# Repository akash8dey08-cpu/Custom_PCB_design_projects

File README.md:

# Embedded Hardware & PCB Design Portfolio (KiCad)

A collection of custom 2-layer printed circuit boards designed in KiCad for power regulation, STM32 sensor telemetry, and analog signal conditioning.

## Projects Index

| Project | Key ICs / Components | Layers | Directory |
| :--- | :--- | :--- | :--- |
| **1. Dual-Input Buck + LDO Power Supply** | `LM2596T-ADJ`, `MIC29152WT`, `1N5822`, USB-C + Barrel Jack | 2-Layer | [`/01-Dual-Input-Power-Supply`](Dual-Input-Power-Supply) |
| **2. STM32 Blackpill Sensor Carrier** | `AMS1117-3.3`, `MPU6050`, `BME280`, `HC-SR04`, `DHT22` | 2-Layer | [`/02-Blackpill-Sensor-Carrier`](LDR_Sensor_Breakout) |
| **3. LDR07 Light Sensor Breakout** | `LDR07`, `10k` Divider, 3-Pin Header | 2-Layer | [`/03-LDR07-Light-Sensor-Breakout`](STM_sensor_hub) |

---

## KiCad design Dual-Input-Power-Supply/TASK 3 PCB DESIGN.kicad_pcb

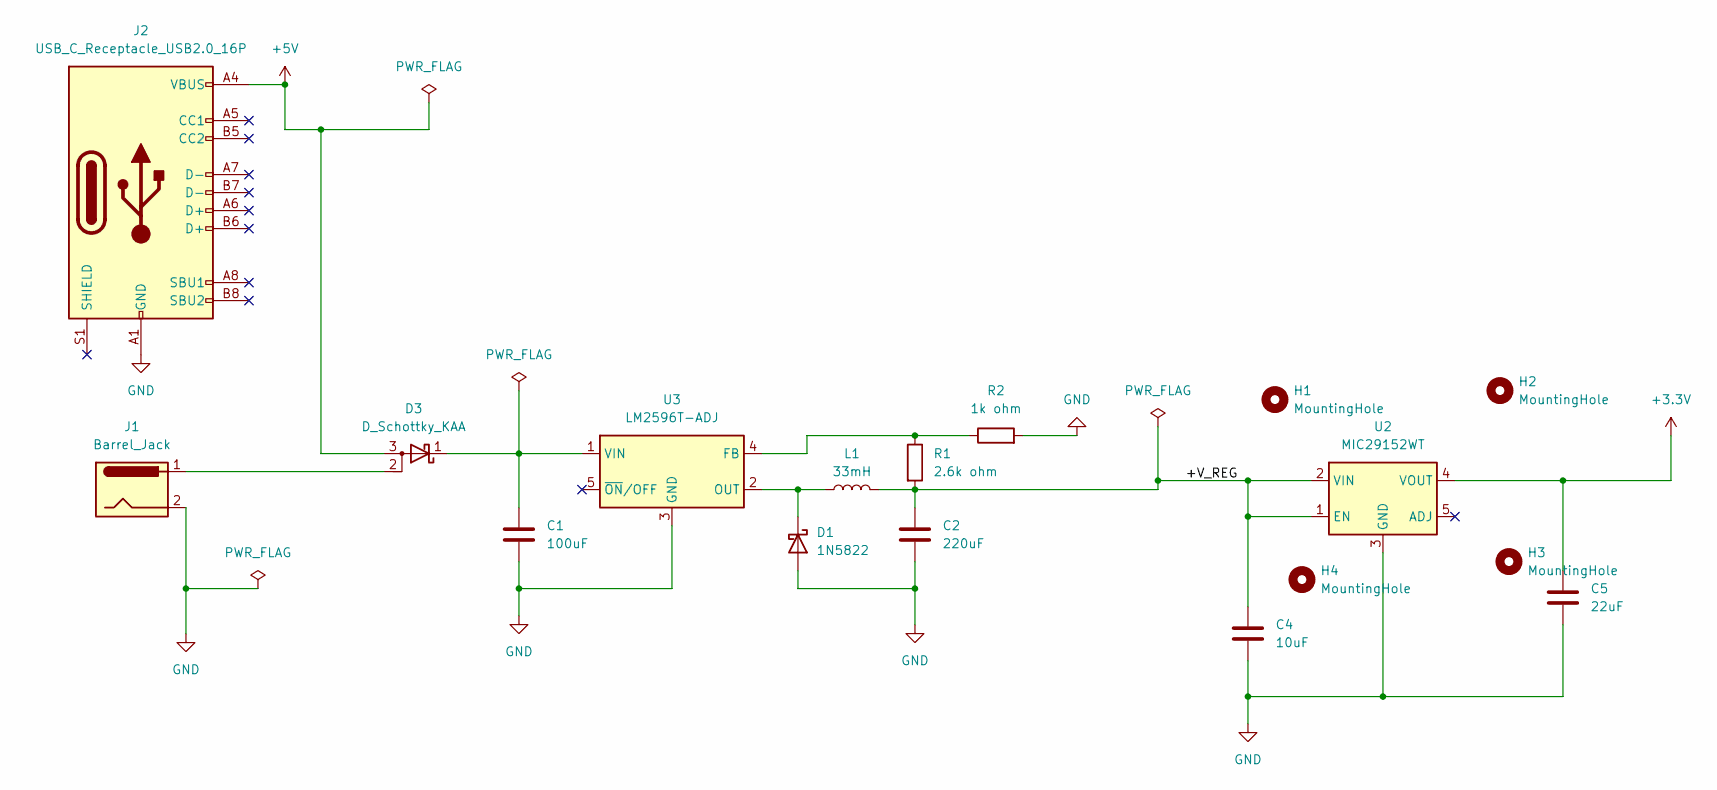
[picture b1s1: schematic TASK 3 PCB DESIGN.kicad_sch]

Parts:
C1: 100uF; C_1206_3216Metric
C2: 220uF; C_1206_3216Metric
C4: 10uF; C_1206_3216Metric
C5: 22uF; C_1206_3216Metric
D1: 1N5822; D_DO-201AD_P15.24mm_Horizontal
D3: D_Schottky_KAA; TO-220-3_Vertical
H1, H2, H3, H4: MountingHole; MountingHole_3.2mm_M3
J1: Barrel_Jack; BarrelJack_Horizontal
J2: USB_C_Receptacle_USB2.0_16P; USB_C_Receptacle_HRO_TYPE-C-31-M-12
L1: 33mH; L_6.3x6.3_H3
R1: 2.6k ohm; R_0201_0603Metric
R2: 1k ohm; R_0201_0603Metric
U2: MIC29152WT; TO-220-5_P3.4x3.7mm_StaggerEven_Lead3.8mm_Vertical
U3: LM2596T-ADJ; TO-220-5_P3.4x3.7mm_StaggerOdd_Lead3.8mm_Vertical

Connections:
+3.3V: C5.1, U2.4 (VOUT)
+5V: D3.3 (A), J2.A4 (VBUS), J2.A9 (VBUS), J2.B4 (VBUS), J2.B9 (VBUS)
/+V_REG: C2.1, C4.1, L1.2, R1.2, U2.1 (EN), U2.2 (VIN)
GND: C1.2, C2.2, C4.2, C5.2, D1.2 (A), J1.2, J2.A1 (GND), J2.A12 (GND), J2.B1 (GND), J2.B12 (GND), R2.2, U2.3 (GND), U3.3 (GND)
unnamed: D1.1 (K), L1.1, U3.2 (OUT)
unnamed: D3.2 (A), J1.1
unnamed: C1.1, D3.1 (K), U3.1 (VIN)
unnamed: R1.1, R2.1, U3.4 (FB)

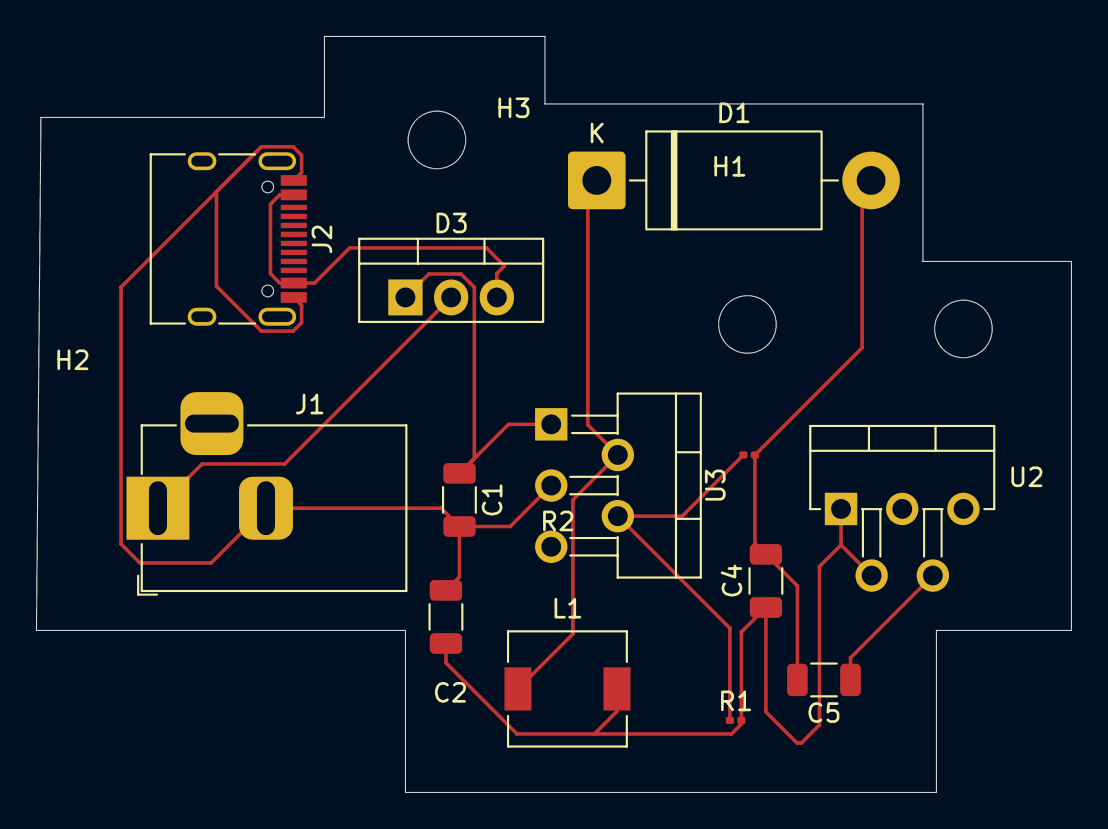
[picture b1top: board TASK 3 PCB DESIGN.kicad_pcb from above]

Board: 2 copper layers, 57.5 x 42.0 mm, 16 parts (0 on the bottom side), 8 nets.

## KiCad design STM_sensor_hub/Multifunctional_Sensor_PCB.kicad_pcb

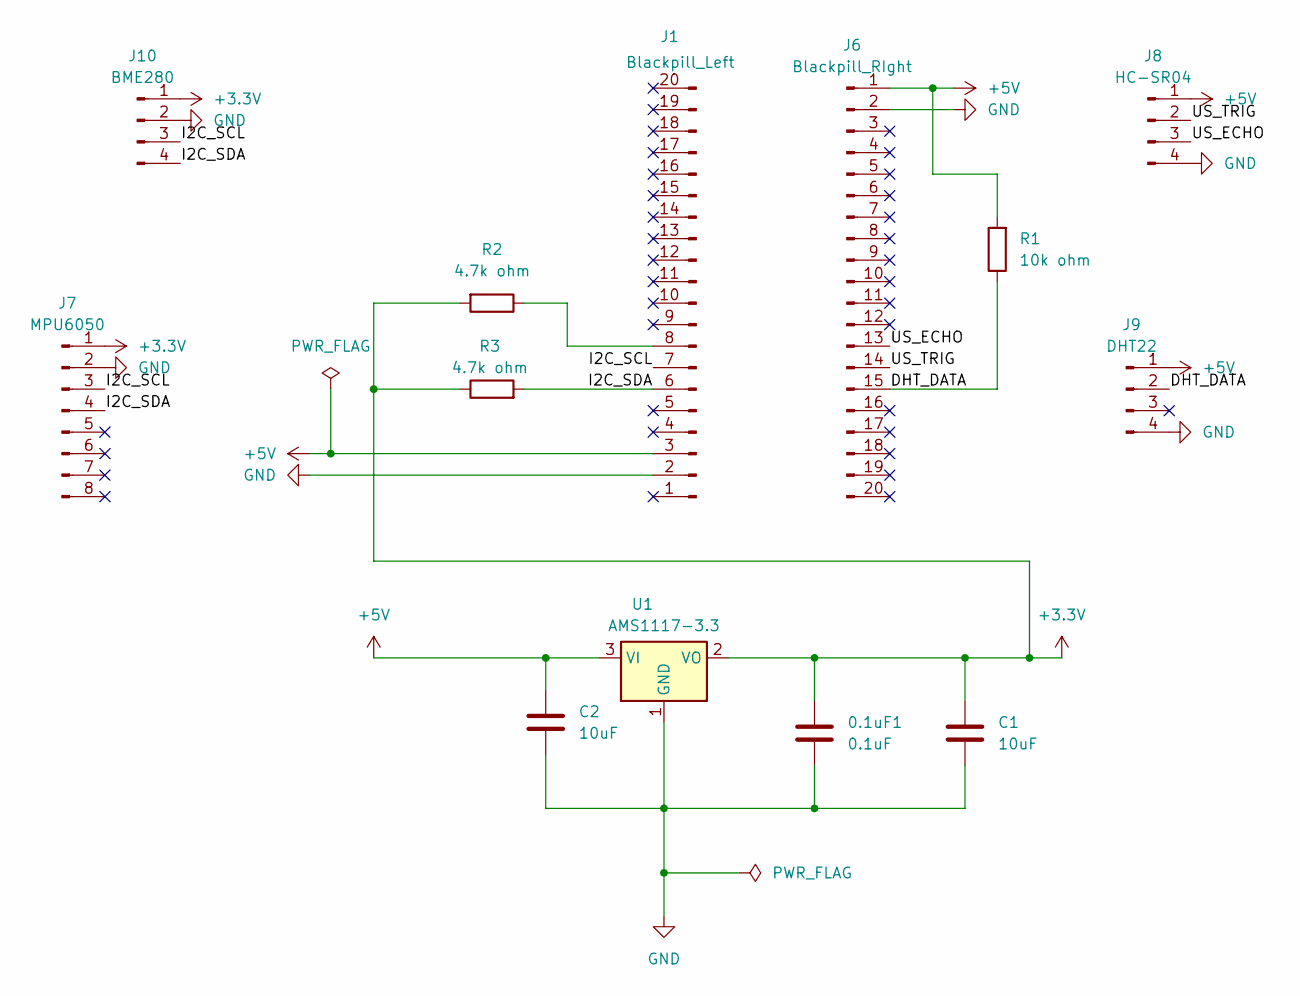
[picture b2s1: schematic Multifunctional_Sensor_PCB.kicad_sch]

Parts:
0.1uF1: 0.1uF; C_0805_2012Metric
C1, C2: 10uF; C_0805_2012Metric
J1: Blackpill_Left; PinHeader_1x20_P2.54mm_Vertical
J6: Blackpill_RIght; PinHeader_1x20_P2.54mm_Vertical
J7: MPU6050; PinHeader_1x08_P2.54mm_Vertical
J8: HC-SR04; PinHeader_1x04_P2.54mm_Vertical
J9: DHT22; PinHeader_1x08_P2.54mm_Vertical
J10: BME280; PinHeader_1x08_P2.54mm_Vertical
R1: 10k ohm; R_0805_2012Metric
R2, R3: 4.7k ohm; R_0805_2012Metric
U1: AMS1117-3.3; SOT-223-3_TabPin2

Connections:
+3.3V: 0.1uF1.1, C1.1, J7.1, J10.1, R2.2, R3.1, U1.2 (VO)
+5V: C2.1, J1.3, J6.1, J8.1, J9.1, R1.2, U1.3 (VI)
/DHT_DATA: J6.15, J9.2, R1.1
/I2C_SCL: J1.7, J7.3, J10.3
/I2C_SDA: J1.6, J7.4, J10.4, R3.2
/US_ECHO: J6.13, J8.3
/US_TRIG: J6.14, J8.2
GND: 0.1uF1.2, C1.2, C2.2, J1.2, J6.2, J7.2, J8.4, J9.4, J10.2, U1.1 (GND)
unnamed: J1.8, R2.1

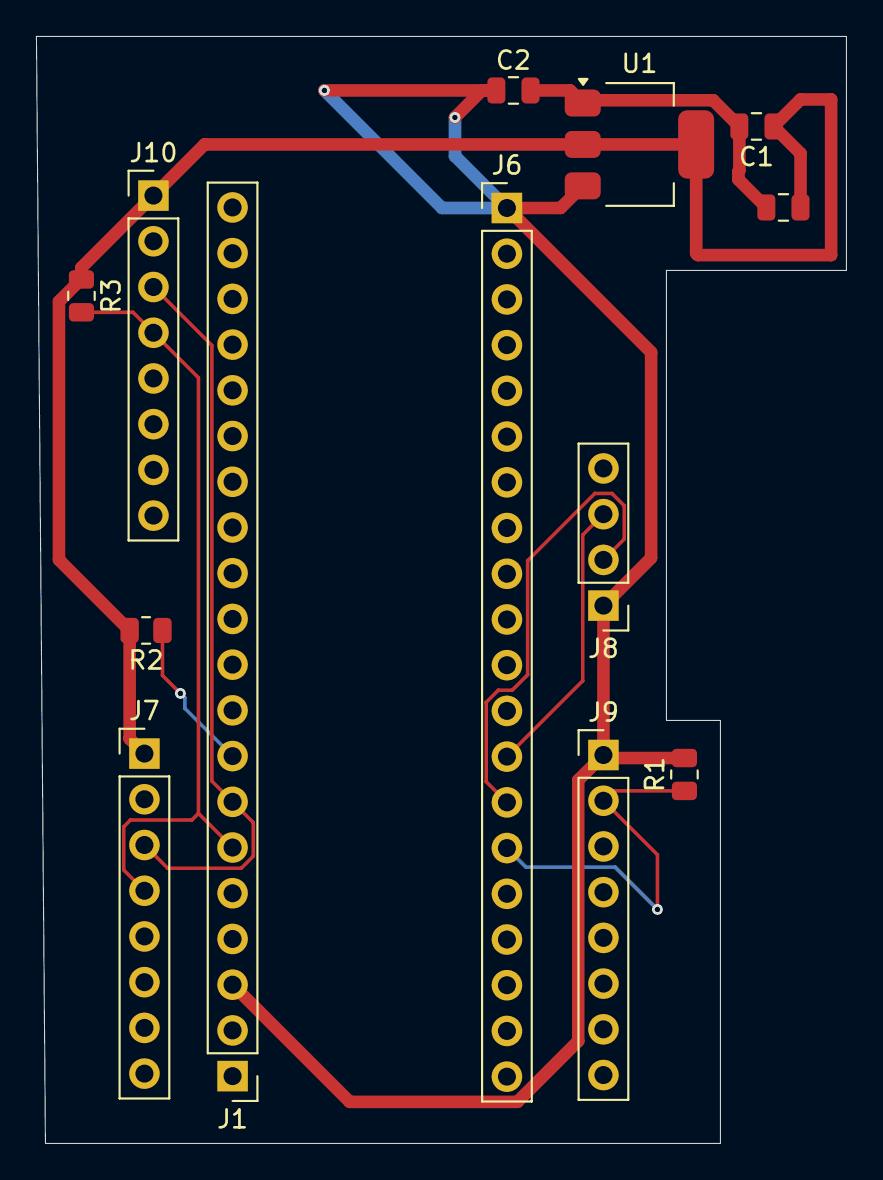
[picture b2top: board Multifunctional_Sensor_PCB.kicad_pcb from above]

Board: 2 copper layers, 45.0 x 61.5 mm, 13 parts (0 on the bottom side), 9 nets.

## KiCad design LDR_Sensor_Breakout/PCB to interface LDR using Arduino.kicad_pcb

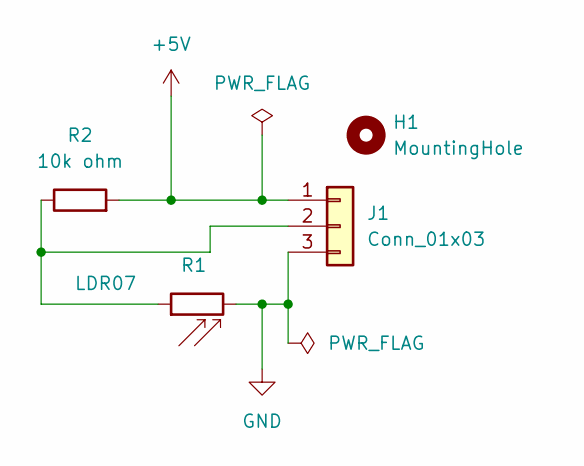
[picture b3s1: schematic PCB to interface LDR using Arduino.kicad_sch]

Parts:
H1: MountingHole; MountingHole_3.2mm_M3
J1: Conn_01x03; PinHeader_1x03_P2.54mm_Vertical
R1: LDR07; R_LDR_5.1x4.3mm_P3.4mm_Vertical
R2: 10k ohm; R_Axial_DIN0207_L6.3mm_D2.5mm_P7.62mm_Horizontal

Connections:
+5V: J1.1, R2.2
GND: J1.3, R1.2
unnamed: J1.2, R1.1, R2.1

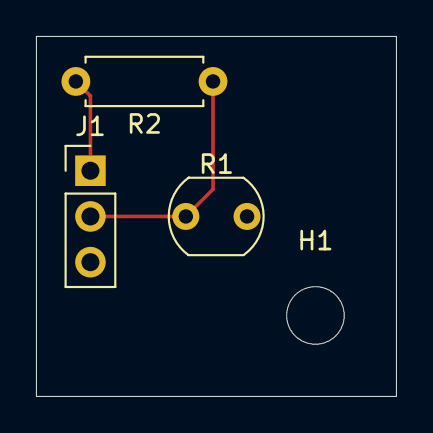
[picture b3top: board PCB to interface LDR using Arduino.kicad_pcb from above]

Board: 2 copper layers, 20.0 x 20.0 mm, 4 parts (0 on the bottom side), 3 nets.
